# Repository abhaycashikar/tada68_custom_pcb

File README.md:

# tada68_custom_pcb
See details and pictures on [my website](https://abhaycashikar.github.io/keyboard_pcb.html)!

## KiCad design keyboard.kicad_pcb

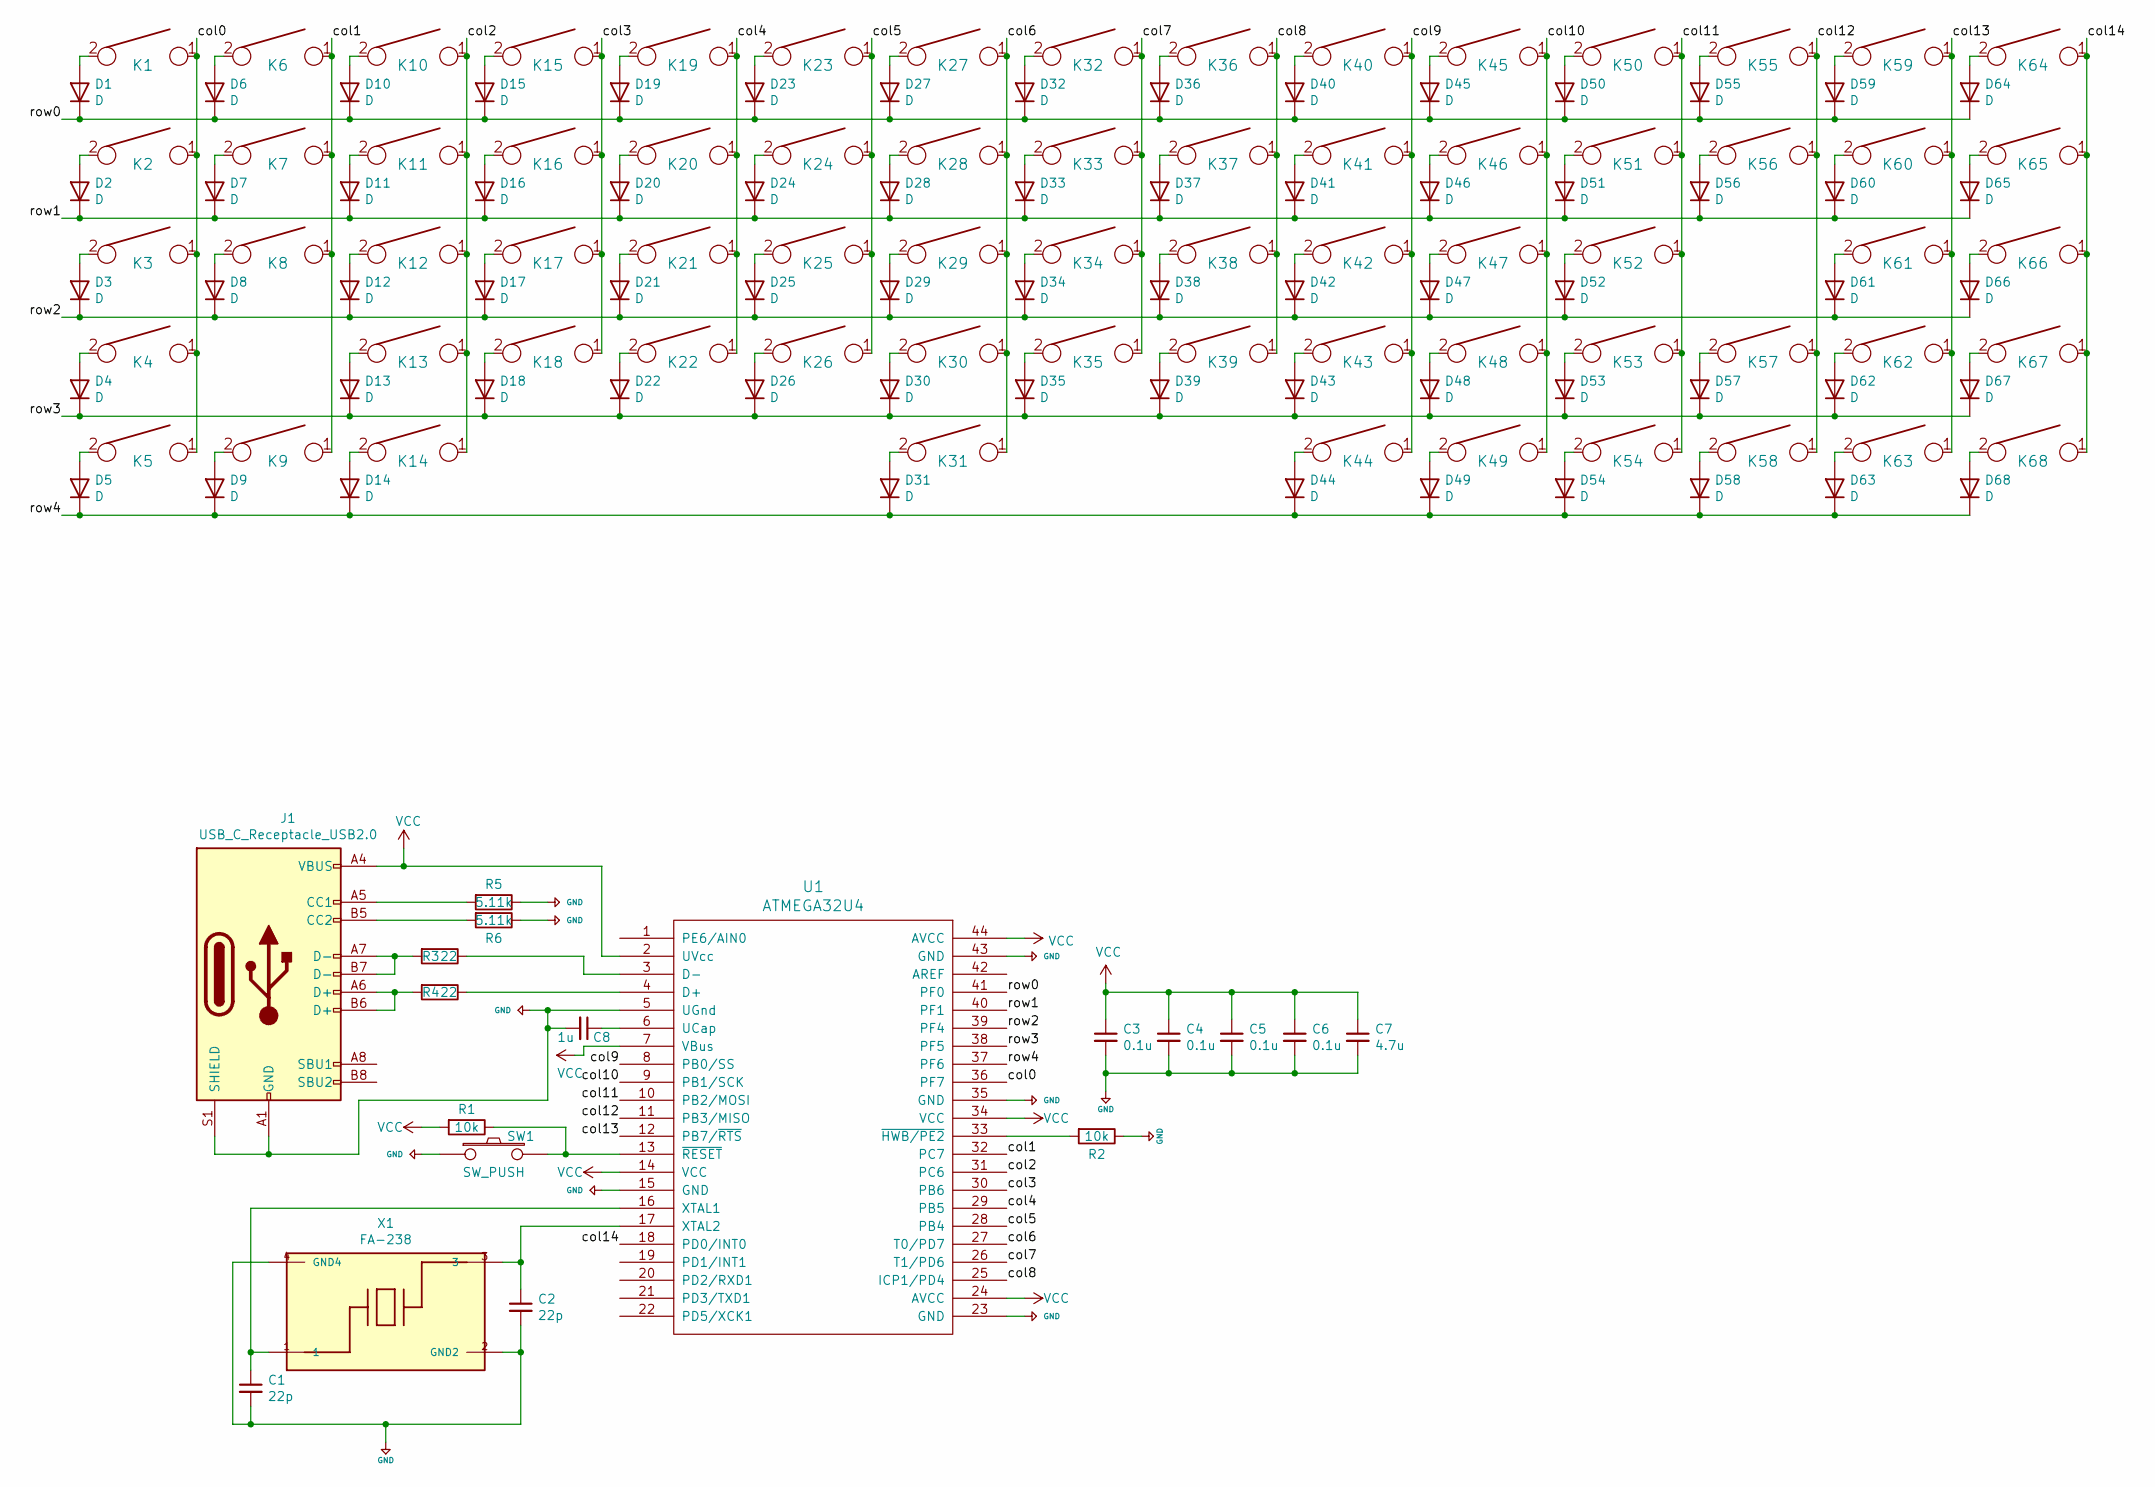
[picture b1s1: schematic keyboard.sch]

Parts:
C1, C2: 22p; C_0805_2012Metric_Pad1.18x1.45mm_HandSolder
C3, C4, C5, C6: 0.1u; C_0805_2012Metric_Pad1.18x1.45mm_HandSolder
C7: 4.7u; C_0805_2012Metric_Pad1.18x1.45mm_HandSolder
C8: 1u; C_0805_2012Metric_Pad1.18x1.45mm_HandSolder
D1, D2, D3, D4, D5, D6, D7, D8, D9, D10, D11, D12, D13, D14, D15, D16, D17, D18, D19, D20, D21, D22, D23, D24, D25, D26, D27, D28, D29, D30, D31, D32, D33, D34, D35, D36, D37, D38, D39, D40, D41, D42, D43, D44, D45, D46, D47, D48, D49, D50, D51, D52, D53, D54, D55, D56, D57, D58, D59, D60, D61, D62, D63, D64, D65, D66, D67, D68: D; D_SOD123_axial
J1: USB_C_Receptacle_USB2.0; USB_C_Receptacle_HRO_TYPE-C-31-M-12
K1, K6, K7, K8, K10, K11, K12, K13, K15, K16, K17, K18, K19, K20, K21, K22, K23, K24, K25, K26, K27, K28, K29, K30, K32, K33, K34, K35, K36, K37, K38, K39, K40, K41, K42, K43, K44, K45, K46, K47, K48, K49, K50, K51, K52, K53, K54, K55, K56, K58, K62, K63, K64, K65, K66, K67, K68: KEYSW; Mx_Alps_100
K2, K60: KEYSW; Mx_Alps_150
K3, K57: KEYSW; Mx_Alps_175
K4, K61: KEYSW; Mx_Alps_225
K5, K9, K14: KEYSW; Mx_Alps_125
K31: KEYSW; Mx_Alps_625
K59: KEYSW; Mx_Alps_200
R1, R2: 10k; R_0805_2012Metric_Pad1.20x1.40mm_HandSolder
R3, R4: 22; R_0805_2012Metric_Pad1.20x1.40mm_HandSolder
R5, R6: 5.11k; R_0805_2012Metric_Pad1.20x1.40mm_HandSolder
SW1: SW_PUSH; SW_SPST_TL3342
U1: ATMEGA32U4; TQFP-44_10x10mm_P0.8mm
X1: FA-238; OSCCC320X250X70-4N

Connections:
+5V: C1.2, C2.2, C3.2, C4.2, C5.2, C6.2, C7.2, C8.2, J1.A1 (GND), J1.A12 (GND), J1.B1 (GND), J1.B12 (GND), J1.S1 (SHIELD), R2.1, R5.1, R6.1, SW1.1, U1.5 (UGnd), U1.15 (GND), U1.23 (GND), U1.35 (GND), U1.43 (GND), X1.2 (GND2), X1.4 (GND4)
/col0: K1.1, K2.1, K3.1, K4.1, K5.1, U1.36 (PF7)
/col1: K6.1, K7.1, K8.1, K9.1, U1.32 (PC7)
/col2: K10.1, K11.1, K12.1, K13.1, K14.1, U1.31 (PC6)
/col3: K15.1, K16.1, K17.1, K18.1, U1.30 (PB6)
/col4: K19.1, K20.1, K21.1, K22.1, U1.29 (PB5)
/col5: K23.1, K24.1, K25.1, K26.1, U1.28 (PB4)
/col6: K27.1, K28.1, K29.1, K30.1, K31.1, U1.27 (T0/PD7)
/col7: K32.1, K33.1, K34.1, K35.1, U1.26 (T1/PD6)
/col8: K36.1, K37.1, K38.1, K39.1, U1.25 (ICP1/PD4)
/col9: K40.1, K41.1, K42.1, K43.1, K44.1, U1.8 (PB0/SS)
/col10: K45.1, K46.1, K47.1, K48.1, K49.1, U1.9 (PB1/SCK)
/col11: K50.1, K51.1, K52.1, K53.1, K54.1, U1.10 (PB2/MOSI)
/col12: K55.1, K56.1, K57.1, K58.1, U1.11 (PB3/MISO)
/col13: K59.1, K60.1, K61.1, K62.1, K63.1, U1.12 (PB7/~RTS)
/col14: K64.1, K65.1, K66.1, K67.1, K68.1, U1.18 (PD0/INT0)
/row0: D1.1 (K), D6.1 (K), D10.1 (K), D15.1 (K), D19.1 (K), D23.1 (K), D27.1 (K), D32.1 (K), D36.1 (K), D40.1 (K), D45.1 (K), D50.1 (K), D55.1 (K), D59.1 (K), D64.1 (K), U1.41 (PF0)
/row1: D2.1 (K), D7.1 (K), D11.1 (K), D16.1 (K), D20.1 (K), D24.1 (K), D28.1 (K), D33.1 (K), D37.1 (K), D41.1 (K), D46.1 (K), D51.1 (K), D56.1 (K), D60.1 (K), D65.1 (K), U1.40 (PF1)
/row2: D3.1 (K), D8.1 (K), D12.1 (K), D17.1 (K), D21.1 (K), D25.1 (K), D29.1 (K), D34.1 (K), D38.1 (K), D42.1 (K), D47.1 (K), D52.1 (K), D61.1 (K), D66.1 (K), U1.39 (PF4)
/row3: D4.1 (K), D13.1 (K), D18.1 (K), D22.1 (K), D26.1 (K), D30.1 (K), D35.1 (K), D39.1 (K), D43.1 (K), D48.1 (K), D53.1 (K), D57.1 (K), D62.1 (K), D67.1 (K), U1.38 (PF5)
/row4: D5.1 (K), D9.1 (K), D14.1 (K), D31.1 (K), D44.1 (K), D49.1 (K), D54.1 (K), D58.1 (K), D63.1 (K), D68.1 (K), U1.37 (PF6)
unnamed: C1.1, U1.16 (XTAL1), X1.1
unnamed: C2.1, U1.17 (XTAL2), X1.3
unnamed: C8.1, U1.6 (UCap)
unnamed: D1.2 (A), K1.2
unnamed: D2.2 (A), K2.2
unnamed: D3.2 (A), K3.2
unnamed: D4.2 (A), K4.2
unnamed: D5.2 (A), K5.2
unnamed: D6.2 (A), K6.2
unnamed: D7.2 (A), K7.2
unnamed: D8.2 (A), K8.2
unnamed: D9.2 (A), K9.2
unnamed: D10.2 (A), K10.2
unnamed: D11.2 (A), K11.2
unnamed: D12.2 (A), K12.2
unnamed: D13.2 (A), K13.2
unnamed: D14.2 (A), K14.2
unnamed: D15.2 (A), K15.2
unnamed: D16.2 (A), K16.2
unnamed: D17.2 (A), K17.2
unnamed: D18.2 (A), K18.2
unnamed: D19.2 (A), K19.2
unnamed: D20.2 (A), K20.2
unnamed: D21.2 (A), K21.2
unnamed: D22.2 (A), K22.2
unnamed: D23.2 (A), K23.2
unnamed: D24.2 (A), K24.2
unnamed: D25.2 (A), K25.2
unnamed: D26.2 (A), K26.2
unnamed: D27.2 (A), K27.2
unnamed: D28.2 (A), K28.2
unnamed: D29.2 (A), K29.2
unnamed: D30.2 (A), K30.2
unnamed: D31.2 (A), K31.2
unnamed: D32.2 (A), K32.2
unnamed: D33.2 (A), K33.2
unnamed: D34.2 (A), K34.2
unnamed: D35.2 (A), K35.2
unnamed: D36.2 (A), K36.2
unnamed: D37.2 (A), K37.2
unnamed: D38.2 (A), K38.2
unnamed: D39.2 (A), K39.2
unnamed: D40.2 (A), K40.2
unnamed: D41.2 (A), K41.2
unnamed: D42.2 (A), K42.2
unnamed: D43.2 (A), K43.2
unnamed: D44.2 (A), K44.2
unnamed: D45.2 (A), K45.2
unnamed: D46.2 (A), K46.2
unnamed: D47.2 (A), K47.2
unnamed: D48.2 (A), K48.2
unnamed: D49.2 (A), K49.2
unnamed: D50.2 (A), K50.2
unnamed: D51.2 (A), K51.2
unnamed: D52.2 (A), K52.2
unnamed: D53.2 (A), K53.2
unnamed: D54.2 (A), K54.2
unnamed: D55.2 (A), K55.2
unnamed: D56.2 (A), K56.2
unnamed: D57.2 (A), K57.2
unnamed: D58.2 (A), K58.2
unnamed: D59.2 (A), K59.2
unnamed: D60.2 (A), K60.2
unnamed: D61.2 (A), K61.2
unnamed: D62.2 (A), K62.2
unnamed: D63.2 (A), K63.2
unnamed: D64.2 (A), K64.2
unnamed: D65.2 (A), K65.2
unnamed: D66.2 (A), K66.2
unnamed: D67.2 (A), K67.2
unnamed: D68.2 (A), K68.2
unnamed: J1.A5 (CC1), R5.2
unnamed: J1.A6 (D+), J1.B6 (D+), R4.2
unnamed: J1.A7 (D-), J1.B7 (D-), R3.2
unnamed: J1.B5 (CC2), R6.2
unnamed: R1.1, SW1.2, U1.13 (~RESET)
unnamed: R2.2, U1.33 (~HWB/PE2)
unnamed: R3.1, U1.3 (D-)
unnamed: R4.1, U1.4 (D+)
VCC: C3.1, C4.1, C5.1, C6.1, C7.1, J1.A4 (VBUS), J1.A9 (VBUS), J1.B4 (VBUS), J1.B9 (VBUS), R1.2, U1.2 (UVcc), U1.7 (VBus), U1.14 (VCC), U1.24 (AVCC), U1.34 (VCC), U1.44 (AVCC)

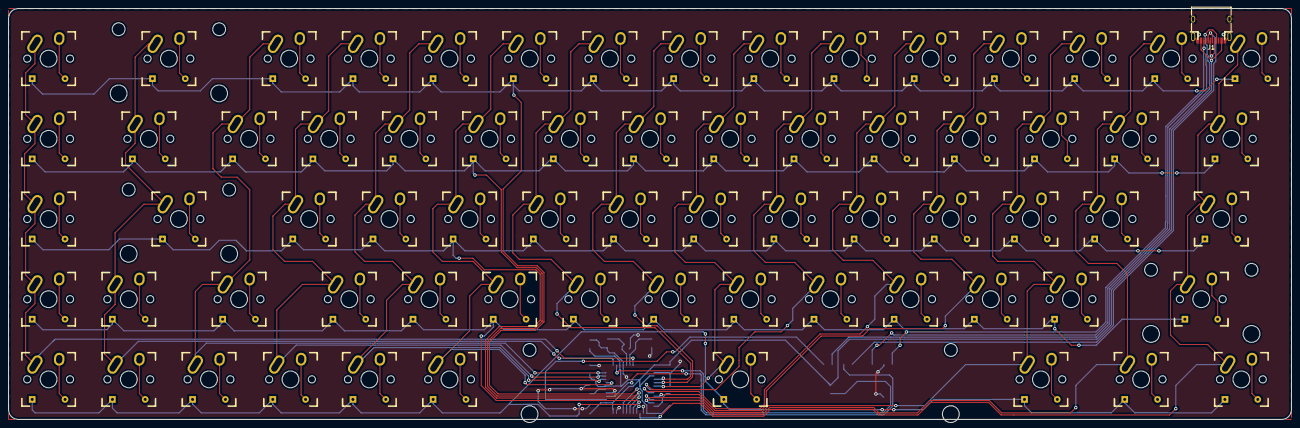
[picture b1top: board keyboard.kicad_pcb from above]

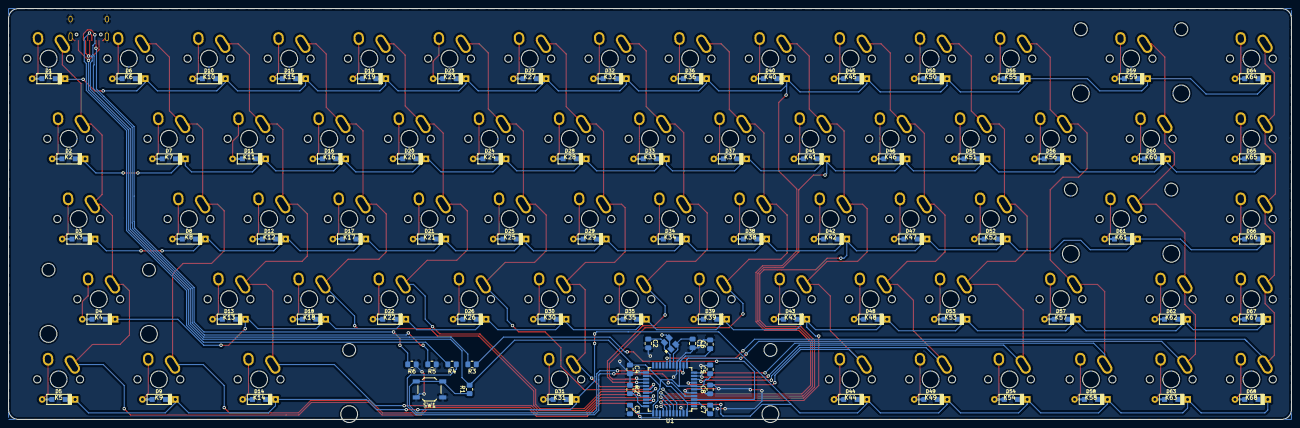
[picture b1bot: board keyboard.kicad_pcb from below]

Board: 2 copper layers, 304.8 x 97.6 mm, 154 parts (85 on the bottom side), 101 nets.
